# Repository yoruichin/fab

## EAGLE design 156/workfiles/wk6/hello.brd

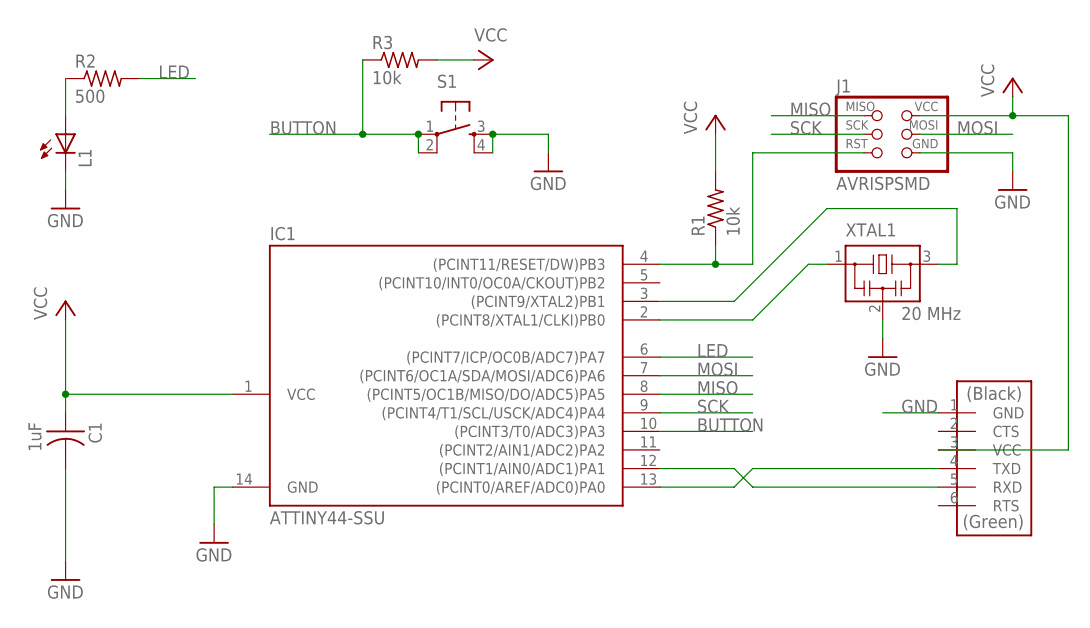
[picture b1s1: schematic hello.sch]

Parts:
C1: 1uF; C1206
IC1: ATTINY44-SSU; SOIC14
J1: AVRISPSMD; 2X03SMD
J2: FTDI; 1X06SMD
L1: LEDFAB1206; LED1206FAB
R1, R3: 10k; R1206
R2: 500; R1206
S1: 6MM_SWITCH6MM_SWITCH; 6MM_SWITCH
XTAL1: 20 MHz; EFOBM

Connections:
BUTTON: IC1.10 ((PCINT3/T0/ADC3)PA3), R3.1, S1.1, S1.2 (P1)
GND: C1.2, IC1.14 (GND), J1.6 (GND), J2.1 (GND), L1.2 (C), S1.3 (S), S1.4 (S1), XTAL1.2
LED: IC1.6 ((PCINT7/ICP/OC0B/ADC7)PA7), R2.2
MISO: IC1.8 ((PCINT5/OC1B/MISO/DO/ADC5)PA5), J1.1 (MISO)
MOSI: IC1.7 ((PCINT6/OC1A/SDA/MOSI/ADC6)PA6), J1.4 (MOSI)
unnamed: L1.1 (A), R2.1
unnamed: IC1.3 ((PCINT9/XTAL2)PB1), XTAL1.3
unnamed: IC1.2 ((PCINT8/XTAL1/CLKI)PB0), XTAL1.1
unnamed: IC1.4 ((PCINT11/RESET/DW)PB3), J1.5 (RST), R1.1
unnamed: IC1.12 ((PCINT1/AIN0/ADC1)PA1), J2.5 (RXD)
unnamed: IC1.13 ((PCINT0/AREF/ADC0)PA0), J2.4 (TXD)
SCK: IC1.9 ((PCINT4/T1/SCL/USCK/ADC4)PA4), J1.3 (SCK)
VCC: C1.1, IC1.1 (VCC), J1.2 (VCC), J2.3 (VCC), R1.2, R3.2

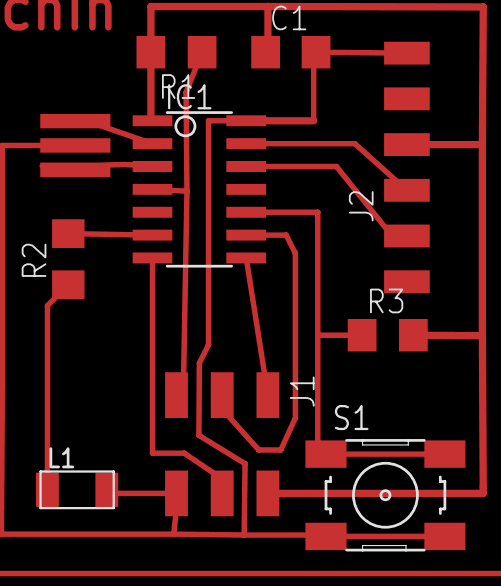
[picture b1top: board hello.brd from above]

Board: 2 copper layers, 10 parts (0 on the bottom side), 13 nets.

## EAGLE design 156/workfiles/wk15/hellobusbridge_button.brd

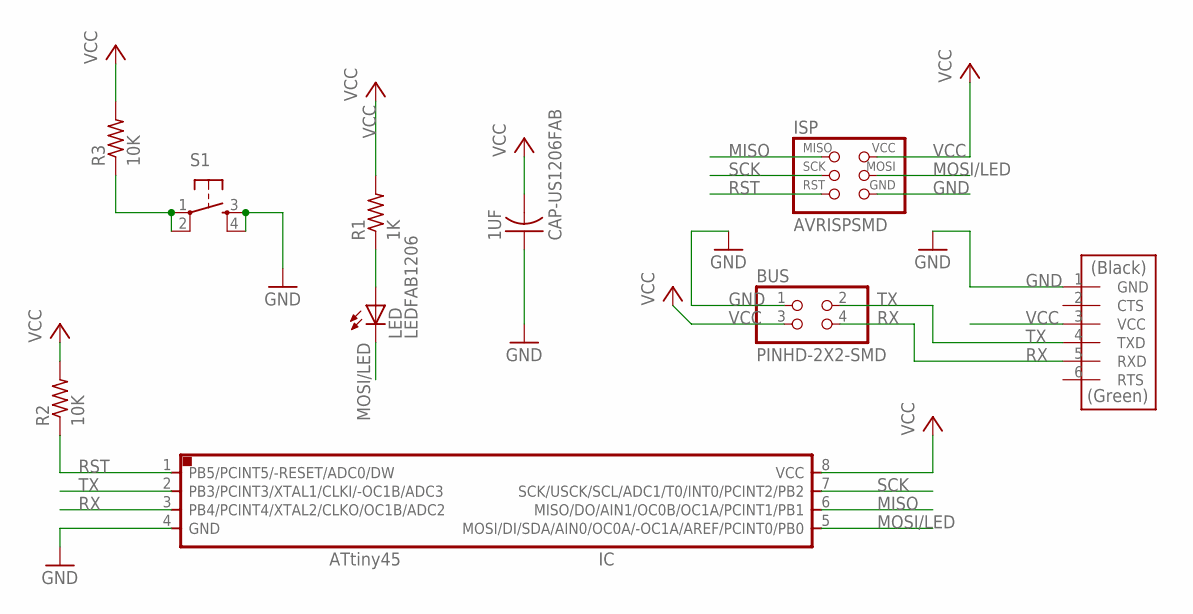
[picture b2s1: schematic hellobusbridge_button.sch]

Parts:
1UF: CAP-US1206FAB; C1206FAB
BUS: PINHD-2X2-SMD; 2X02SMD
IC: IC; SOIC8
ISP: AVRISPSMD; 2X03SMD
LED: LEDFAB1206; LED1206FAB
R1: 1K; R1206FAB
R2, R3: 10K; R1206FAB
S1: 6MM_SWITCH6MM_SWITCH; 6MM_SWITCH
U$5: FTDI-SMD-HEADER; 1X06SMD

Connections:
GND: 1UF.1, BUS.1, IC.4 (GND), ISP.6 (GND), S1.3 (S), S1.4 (S1), U$5.1 (GND)
MISO: IC.6 (MISO/DO/AIN1/OC0B/OC1A/PCINT1/PB1), ISP.1 (MISO), R3.1, S1.1, S1.2 (P1)
MOSI/LED: IC.5 (MOSI/DI/SDA/AIN0/OC0A/-OC1A/AREF/PCINT0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), ISP.4 (MOSI), LED.2 (C)
unnamed: LED.1 (A), R1.1
RST: IC.1 (PB5/PCINT5/-RESET/ADC0/DW), ISP.5 (RST), R2.1
RX: BUS.4, IC.3 (PB4/PCINT4/XTAL2/CLKO/OC1B/ADC2), U$5.5 (RXD)
SCK: IC.7 (SCK/USCK/SCL/ADC1/T0/INT0/PCINT2/PB2), ISP.3 (SCK)
TX: BUS.2, IC.2 (PB3/PCINT3/XTAL1/CLKI/-OC1B/ADC3), U$5.4 (TXD)
VCC: 1UF.2, BUS.3, IC.8 (VCC), ISP.2 (VCC), R1.2, R2.2, R3.2, U$5.3 (VCC)

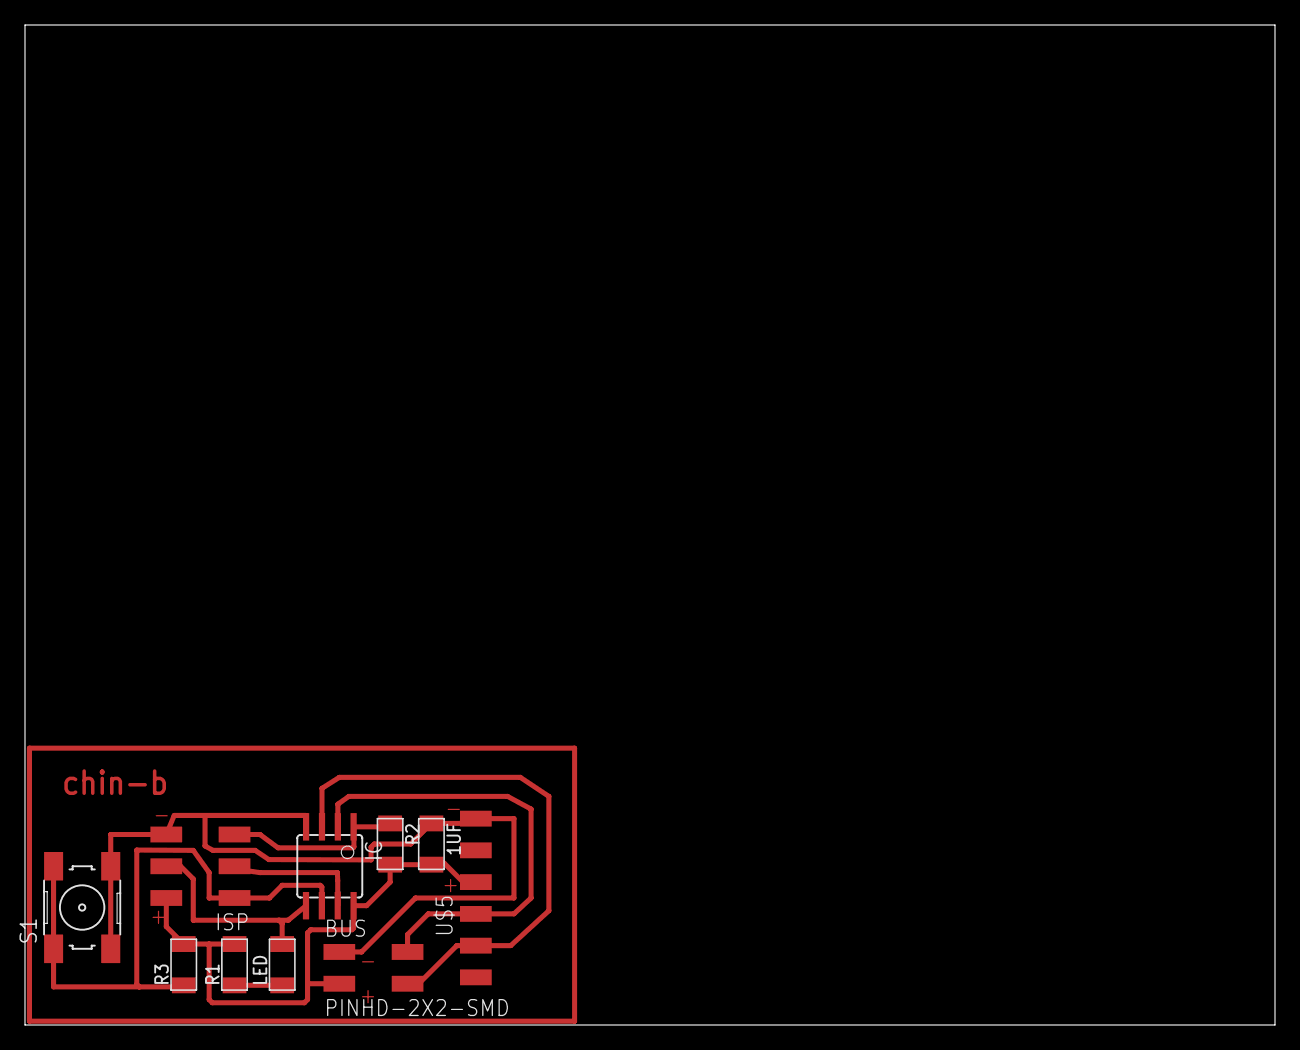
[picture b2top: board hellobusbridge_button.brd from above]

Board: 2 copper layers, 100.0 x 80.0 mm, 10 parts (0 on the bottom side), 9 nets.

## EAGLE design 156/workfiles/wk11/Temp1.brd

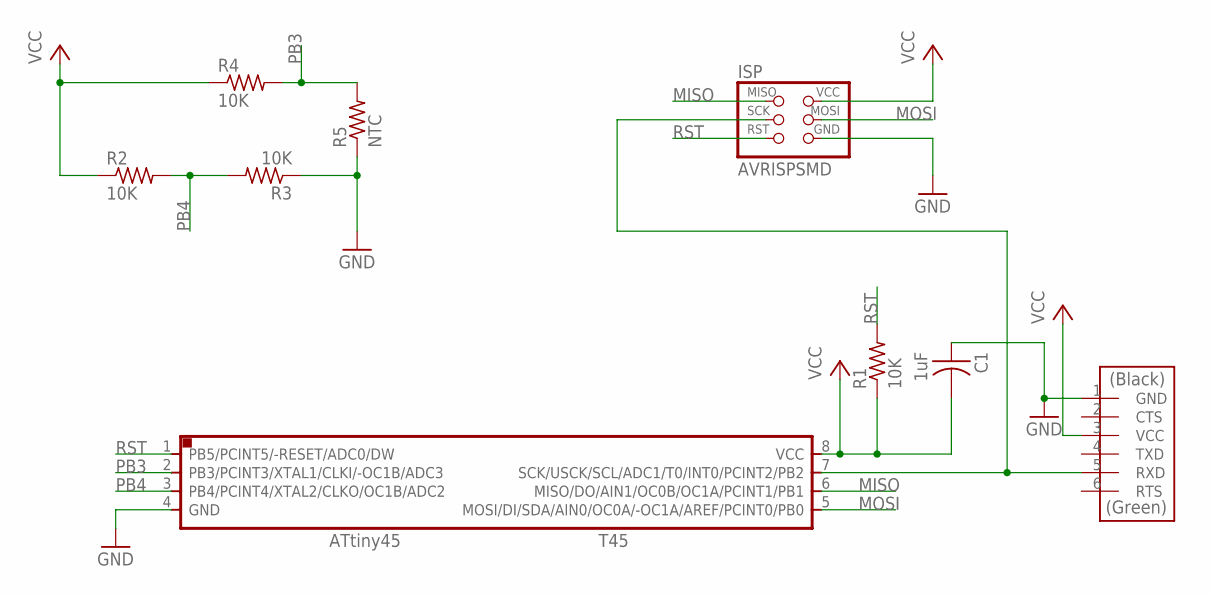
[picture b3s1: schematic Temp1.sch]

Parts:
C1: 1uF; C1206FAB
FDTI: FTDI-SMD-HEADER; 1X06SMD
ISP: AVRISPSMD; 2X03SMD
R1, R2, R3, R4: 10K; R1206FAB
R5: NTC; R1206FAB
T45: ATTINY45SI; SOIC8

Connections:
GND: C1.1, FDTI.1 (GND), ISP.6 (GND), R3.1, R5.1, T45.4 (GND)
MISO: ISP.1 (MISO), T45.6 (MISO/DO/AIN1/OC0B/OC1A/PCINT1/PB1)
MOSI: ISP.4 (MOSI), T45.5 (MOSI/DI/SDA/AIN0/OC0A/-OC1A/AREF/PCINT0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)
unnamed: FDTI.5 (RXD), ISP.3 (SCK), T45.7 (SCK/USCK/SCL/ADC1/T0/INT0/PCINT2/PB2)
PB3: R4.2, R5.2, T45.2 (PB3/PCINT3/XTAL1/CLKI/-OC1B/ADC3)
PB4: R2.2, R3.2, T45.3 (PB4/PCINT4/XTAL2/CLKO/OC1B/ADC2)
RST: ISP.5 (RST), R1.2, T45.1 (PB5/PCINT5/-RESET/ADC0/DW)
VCC: C1.2, FDTI.3 (VCC), ISP.2 (VCC), R1.1, R2.1, R4.1, T45.8 (VCC)

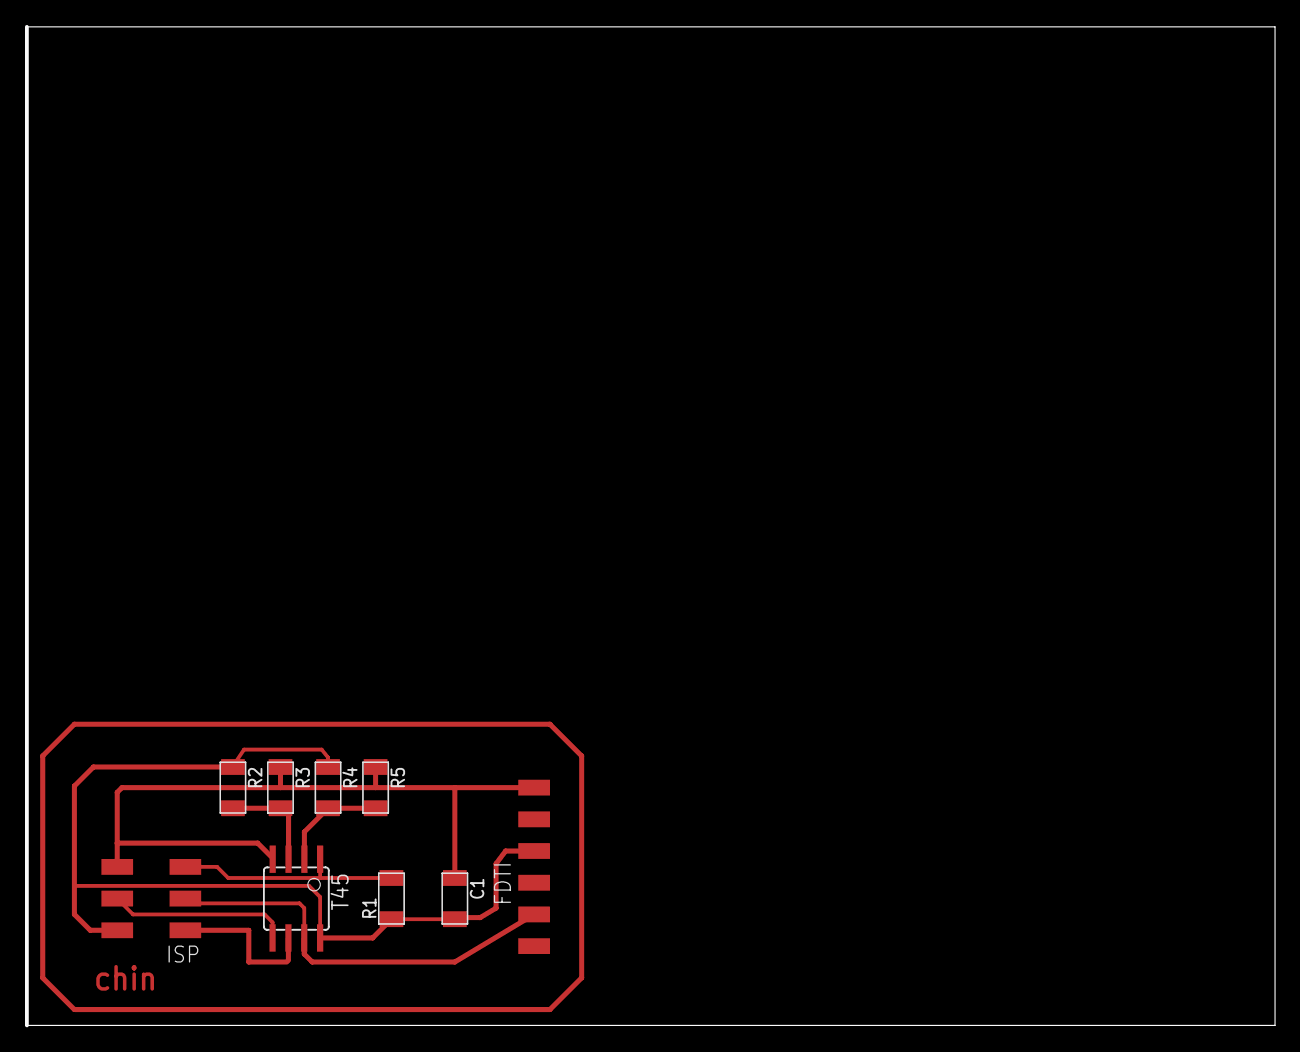
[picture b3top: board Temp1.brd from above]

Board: 2 copper layers, 100.0 x 80.0 mm, 9 parts (0 on the bottom side), 8 nets.

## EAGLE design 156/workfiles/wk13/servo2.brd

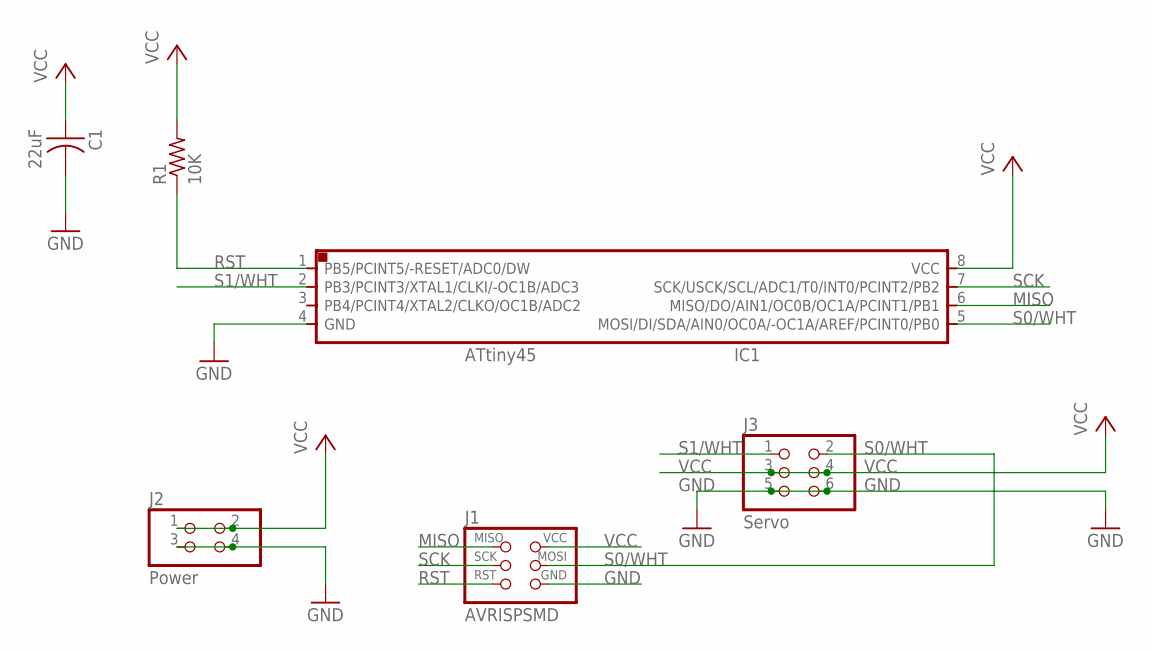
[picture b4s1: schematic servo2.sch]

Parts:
C1: 22uF; C1206FAB
IC1: ATTINY45SI; SOIC8
J1: AVRISPSMD; 2X03SMD
J2: Power; 2X02SMD
J3: Servo; 2X03SMD
R1: 10K; R1206FAB

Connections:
GND: C1.2, IC1.4 (GND), J1.6 (GND), J2.3, J2.4, J3.5, J3.6
MISO: IC1.6 (MISO/DO/AIN1/OC0B/OC1A/PCINT1/PB1), J1.1 (MISO)
RST: IC1.1 (PB5/PCINT5/-RESET/ADC0/DW), J1.5 (RST), R1.1
S0/WHT: IC1.5 (MOSI/DI/SDA/AIN0/OC0A/-OC1A/AREF/PCINT0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), J1.4 (MOSI), J3.2
S1/WHT: IC1.2 (PB3/PCINT3/XTAL1/CLKI/-OC1B/ADC3), J3.1
SCK: IC1.7 (SCK/USCK/SCL/ADC1/T0/INT0/PCINT2/PB2), J1.3 (SCK)
VCC: C1.1, IC1.8 (VCC), J1.2 (VCC), J2.1, J2.2, J3.3, J3.4, R1.2

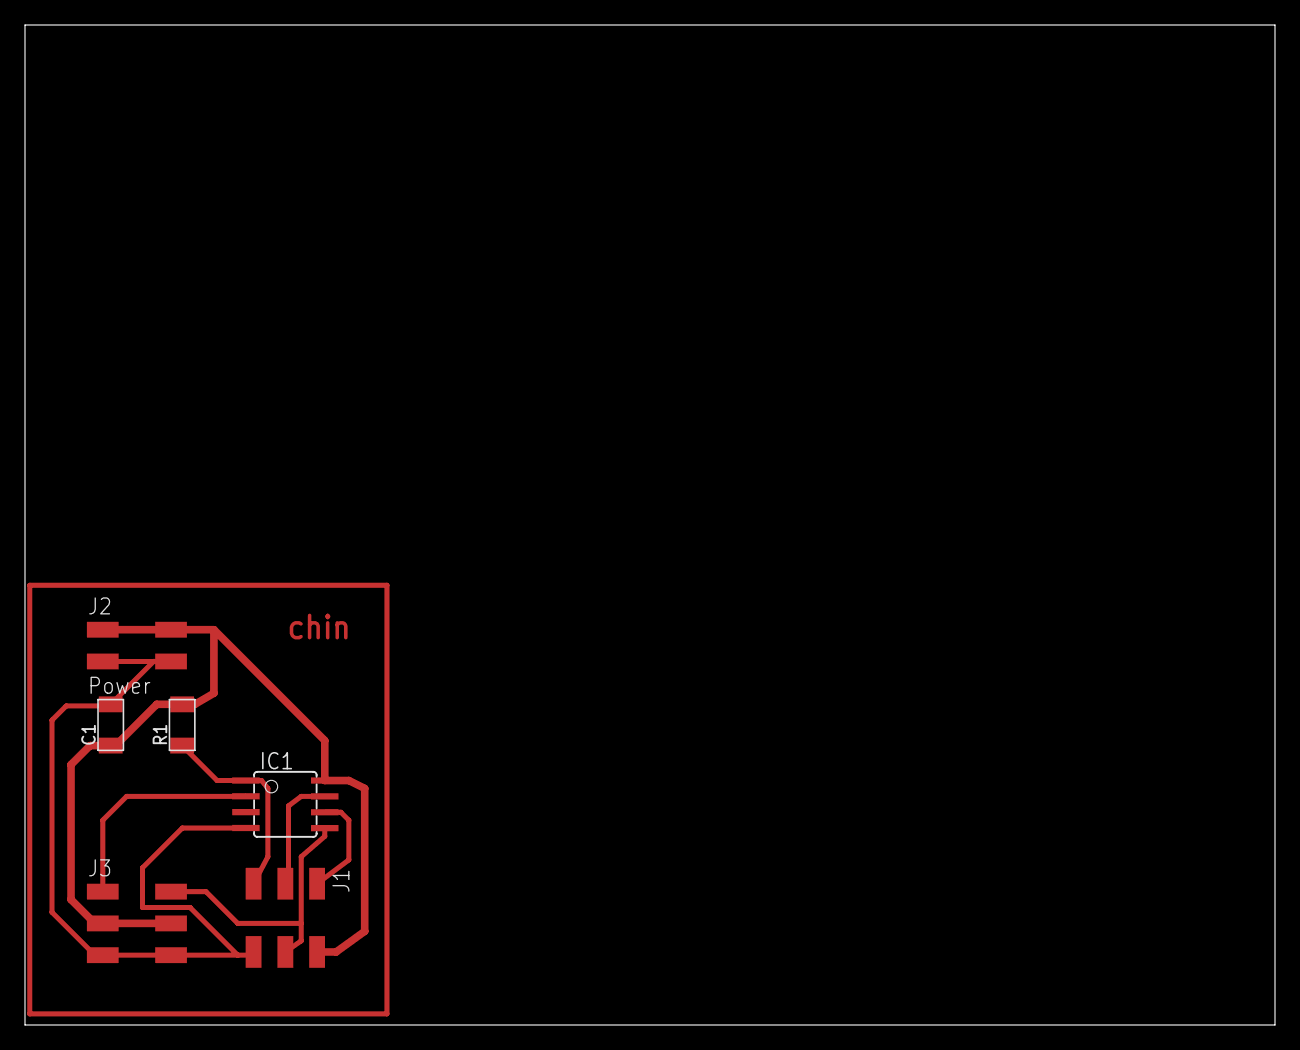
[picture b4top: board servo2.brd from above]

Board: 2 copper layers, 100.0 x 80.0 mm, 6 parts (0 on the bottom side), 7 nets.

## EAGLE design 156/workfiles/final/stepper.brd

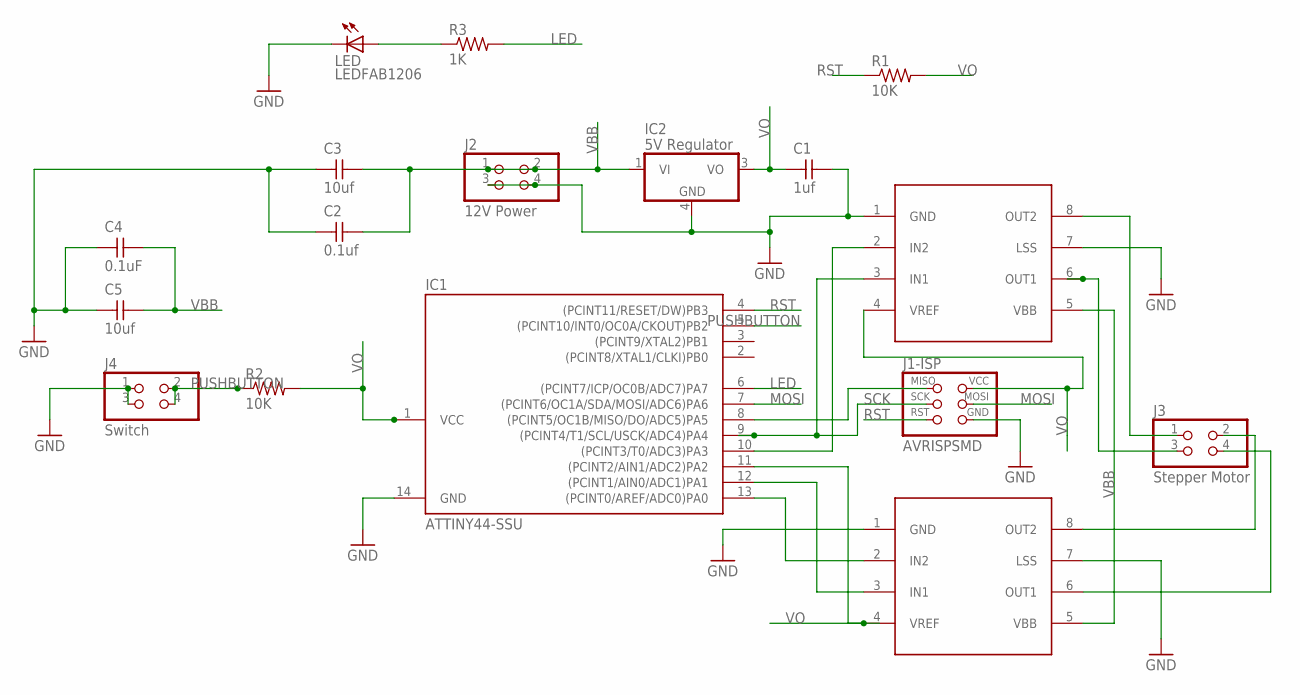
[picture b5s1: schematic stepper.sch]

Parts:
C1: 1uf; C1206FAB
C2: 0.1uf; C1206FAB
C3, C5: 10uf; C1206FAB
C4: 0.1uF; C1206FAB
IC1: ATTINY44-SSU; SOIC14
IC2: 5V Regulator; SOT223
IC3, IC4: A4950; SOIC8
J1-ISP: AVRISPSMD; 2X03SMD
J2: 12V Power; 2X02SMD
J3: Stepper Motor; 2X02SMD
J4: Switch; 2X02SMD
LED: LEDFAB1206; LED1206FAB
R1, R2: 10K; R1206FAB
R3: 1K; R1206FAB

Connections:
GND: C1.2, C2.1, C3.1, C4.1, C5.1, IC1.14 (GND), IC2.4 (GND), IC3.1 (GND), IC3.7 (LSS), IC4.1 (GND), IC4.7 (LSS), J1-ISP.6 (GND), J2.3, J2.4, J4.1, J4.3, LED.2 (C)
LED: IC1.6 ((PCINT7/ICP/OC0B/ADC7)PA7), R3.2
MOSI: IC1.7 ((PCINT6/OC1A/SDA/MOSI/ADC6)PA6), J1-ISP.4 (MOSI)
unnamed: IC1.13 ((PCINT0/AREF/ADC0)PA0), IC3.2 (IN2)
unnamed: IC1.12 ((PCINT1/AIN0/ADC1)PA1), IC3.3 (IN1)
unnamed: IC1.10 ((PCINT3/T0/ADC3)PA3), IC4.2 (IN2)
unnamed: IC4.8 (OUT2), J3.1
unnamed: IC4.6 (OUT1), J3.3
unnamed: IC3.8 (OUT2), J3.2
unnamed: IC1.8 ((PCINT5/OC1B/MISO/DO/ADC5)PA5), J1-ISP.1 (MISO)
unnamed: IC3.6 (OUT1), J3.4
unnamed: LED.1 (A), R3.1
PUSHBUTTON: IC1.5 ((PCINT10/INT0/OC0A/CKOUT)PB2), J4.2, J4.4, R2.1
RST: IC1.4 ((PCINT11/RESET/DW)PB3), J1-ISP.5 (RST), R1.1
SCK: IC1.9 ((PCINT4/T1/SCL/USCK/ADC4)PA4), IC4.3 (IN1), J1-ISP.3 (SCK)
VBB: C2.2, C3.2, C4.2, C5.2, IC2.1 (VI), IC3.5 (VBB), IC4.5 (VBB), J2.1, J2.2
VO: C1.1, IC1.1 (VCC), IC1.11 ((PCINT2/AIN1/ADC2)PA2), IC2.3 (VO), IC3.4 (VREF), IC4.4 (VREF), J1-ISP.2 (VCC), R1.2, R2.2

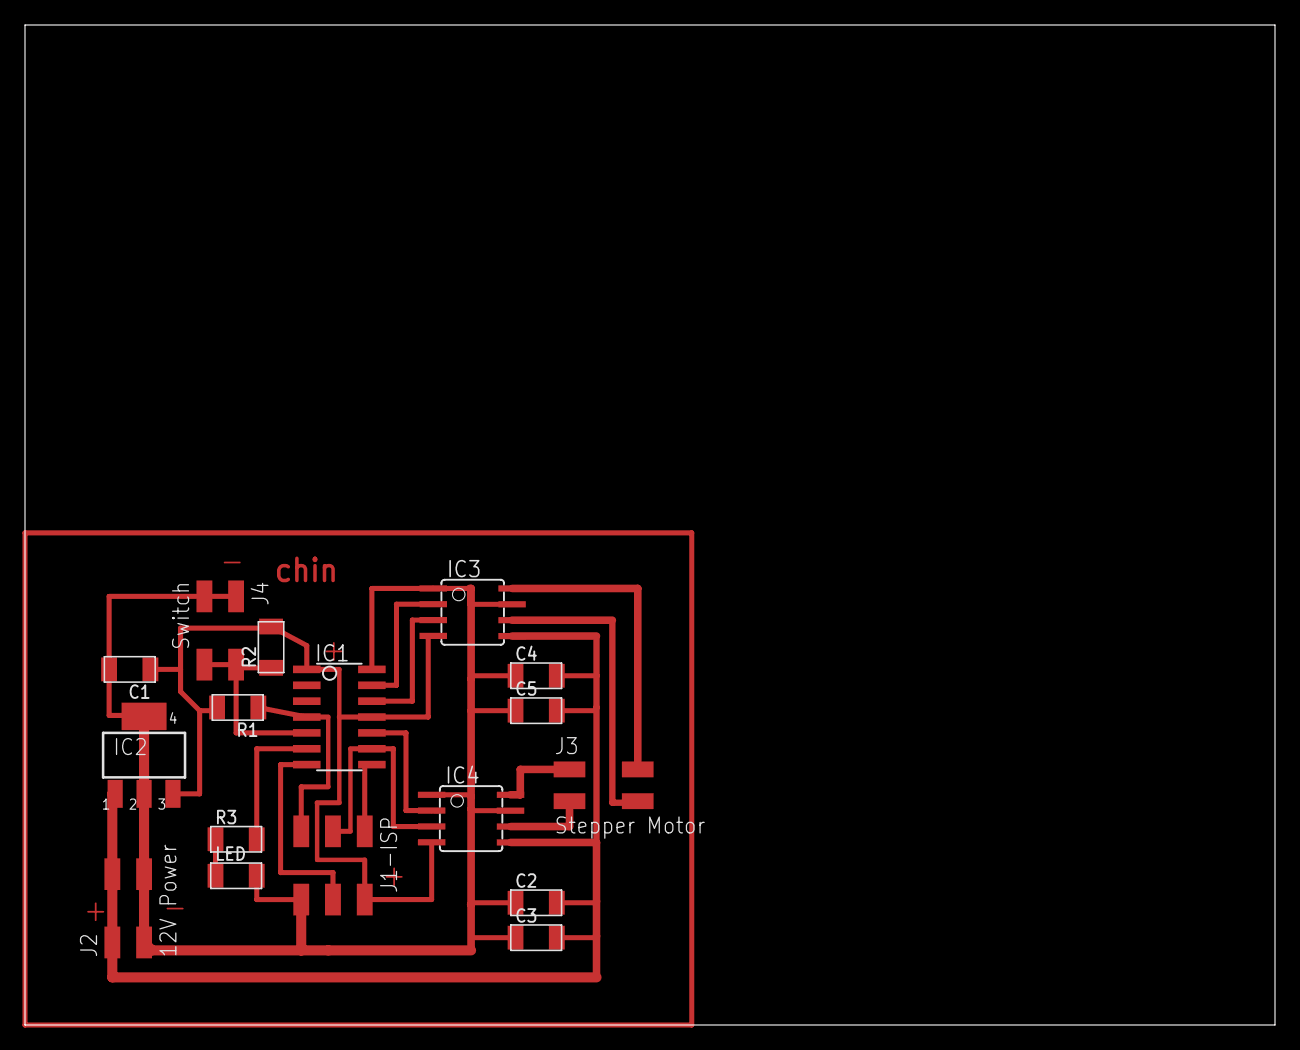
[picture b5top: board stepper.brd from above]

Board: 2 copper layers, 100.0 x 80.0 mm, 17 parts (0 on the bottom side), 17 nets.

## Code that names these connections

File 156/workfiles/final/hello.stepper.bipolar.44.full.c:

//
//
// hello.stepper.bipolar.44.full.c
//
// bipolar full stepping hello-world
//
// Neil Gershenfeld
// 11/21/12
//
// (c) Massachusetts Institute of Technology 2012
// This work may be reproduced, modified, distributed,
// performed, and displayed for any purpose. Copyright is
// retained and must be preserved. The work is provided
// as is; no warranty is provided, and users accept all 
// liability.
//
// Documentation
// =============
// Modified by Yue Siew Chin, Fablab Singapore, 2016
//
// This program causes a stepper motor to turn a page at the press of a pushbutton.
// Microcontroller = ATtiny44
// Pushbutton = PB2
// LED = PA7
// Stepper motor pins = PA0, PA1, PA3, PA4 (A2, A1, B2, B1)
// Bipolar stepper motor 14HS13-0804S
// H-bridge PWM Motor Driver Allegro A4950 
// 5V Regulator LM2940



#include <avr/io.h>
#include <util/delay.h>
#include <avr/interrupt.h>

#define output(directions,pin) (directions |= pin) // set port direction for output
#define input(directions,pin) (directions &= (~pin)) // set port direction for input
#define set(port,pin) (port |= pin) // set port pin
#define clear(port,pin) (port &= (~pin)) // clear port pin
#define toggle(port,pin) (port ^= pin)
#define pin_test(pins,pin) (pins & pin) // test for port pin
#define bit_test(byte,bit) (byte & (1 << bit)) // test for bit set

#define bridge_port PORTA // H-bridge port
#define bridge_direction DDRA // H-bridge direction
#define A2 (1 << PA0) // H-bridge output pins
#define A1 (1 << PA1) // "
#define B2 (1 << PA3) // "
#define B1 (1 << PA4) // "
#define on_delay() _delay_us(35) // PWM on time
#define off_delay() _delay_us(15) // PWM off time
#define PWM_count 100 // number of PWM cycles
#define step_count 53 // number of steps


#define button_port PORTB
#define button_pins PINB
#define button_direction DDRB
#define button (1 << PB2) // set button input pin

#define led_port PORTA
#define led_direction DDRA
#define led (1 << PA7) // set LED output pin


static uint8_t count;

//
// A+ B+ PWM pulse
//
void pulse_ApBp() {
  clear(bridge_port, A2);
  clear(bridge_port, B2);
  set(bridge_port, A1);
  set(bridge_port, B1);
   for (count = 0; count < PWM_count; ++count) {
      set(bridge_port, A1);
      set(bridge_port, B1);
      on_delay();
      clear(bridge_port, A1);
      clear(bridge_port, B1);
      off_delay();
    }
  }
//
// A+ B- PWM pulse
//
void pulse_ApBm() {
  clear(bridge_port, A2);
  clear(bridge_port, B1);
  set(bridge_port, A1);
  set(bridge_port, B2);
   for (count = 0; count < PWM_count; ++count) {
      set(bridge_port, A1);
      set(bridge_port, B2);
      on_delay();
      clear(bridge_port, A1);
      clear(bridge_port, B2);
      off_delay();
    }
  }
//
// A- B+ PWM pulse
//
void pulse_AmBp() {
  clear(bridge_port, A1);
  clear(bridge_port, B2);
  set(bridge_port, A2);
  set(bridge_port, B1);
   for (count = 0; count < PWM_count; ++count) {
      set(bridge_port, A2);
      set(bridge_port, B1);
      on_delay();
      clear(bridge_port, A2);
      clear(bridge_port, B1);
      off_delay();
    }
  }
//
// A- B- PWM pulse
//
void pulse_AmBm() {
  clear(bridge_port, A1);
  clear(bridge_port, B1);
  set(bridge_port, A2);
  set(bridge_port, B2);
   for (count = 0; count < PWM_count; ++count) {
      set(bridge_port, A2);
      set(bridge_port, B2);
      on_delay();
      clear(bridge_port, A2);
      clear(bridge_port, B2);
      off_delay();
    }
  }
//
// clockwise step
//
void step_cw() {
   pulse_ApBp();
   pulse_AmBp();
   pulse_AmBm();
   pulse_ApBm();
}
//
// counter-clockwise step
//
void step_ccw() {
   pulse_ApBm();
   pulse_AmBm();
   pulse_AmBp();
   pulse_ApBp();
}

uint8_t debounce(void) {                      // check for button bounce
  if (bit_is_clear(button_pins, button)) {     // button is pressed
    _delay_us(1000);                          // debounce timeout in microseconds
    if (bit_is_clear(button_pins, button)) {   // button is still pressed after a short delay
      return (1);       // return true
    }
  }
  return (0);           // otherwise return false
} 

int main(void) {
   //
   // main
   //
   static uint8_t i,j;
   //
   // set clock divider to /1
   //
   CLKPR = (1 << CLKPCE);
   CLKPR = (0 << CLKPS3) | (0 << CLKPS2) | (0 << CLKPS1) | (0 << CLKPS0);
   //
   // initialize bridge pins
   //
   clear(bridge_port, A1);
   output(bridge_direction, A1);
   clear(bridge_port, A2);
   output(bridge_direction, A2);
   clear(bridge_port, B1);
   output(bridge_direction, B1);
   clear(bridge_port, B2);
   output(bridge_direction, B2);

   input(button_direction, button);  // clear bit
   // set(button_port, button);         // value = HIGH; enable pull-up on the button
   output(led_direction, led);   // set bit of LED for output
   set(led_port, led);

   //
   // main loop
   //
  while (1) {

    if (bit_is_clear(PINB, PB2)) {
      clear(led_port, led); 
      for (i = 0; i < step_count; ++i) {
//          for (j = 0; j < i; ++j)
          step_cw();
        _delay_ms(10); 

//  stop stepper motor rotation
           clear(bridge_port, A1);
           clear(bridge_port, A2);
           clear(bridge_port, B1);
           clear(bridge_port, B2);

      }         
    }
    else {
      set(led_port, led);   // indicates ready to receive input
   }
  }
}

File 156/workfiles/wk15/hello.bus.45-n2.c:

//
//
// hello.bus.45.c
//
// 9600 baud serial bus hello-world
//
// Neil Gershenfeld
// 11/24/10
//
// (c) Massachusetts Institute of Technology 2010
// Permission granted for experimental and personal use;
// license for commercial sale available from MIT.
//

#include <avr/io.h>
#include <util/delay.h>
#include <avr/pgmspace.h>
#include <string.h>

#define output(directions,pin) (directions |= pin) // set port direction for output
#define input(directions,pin) (directions &= (~pin)) // set port direction for input
#define set(port,pin) (port |= pin) // set port pin
#define clear(port,pin) (port &= (~pin)) // clear port pin
#define pin_test(pins,pin) (pins & pin) // test for port pin
#define bit_test(byte,bit) (byte & (1 << bit)) // test for bit set
#define bit_delay_time 100 // bit delay for 9600 with overhead
#define bit_delay() _delay_us(bit_delay_time) // RS232 bit delay
#define half_bit_delay() _delay_us(bit_delay_time/2) // RS232 half bit delay
#define led_delay() _delay_ms(100) // LED flash delay

#define led_port PORTB
#define led_direction DDRB
#define led_pin (1 << PB0)

//#define button_port PORTB
//#define button_direction DDRB
//#define button_pin (1 << PB1)

#define serial_port PORTB
#define serial_direction DDRB
#define serial_pins PINB
#define serial_pin_in (1 << PB3)
#define serial_pin_out (1 << PB4)

#define node_id '2'  // to hard code for each host / slave node

void get_char(volatile unsigned char *pins, unsigned char pin, char *rxbyte) {
   //
   // read character into rxbyte on pins pin
   //    assumes line driver (inverts bits)
   //
   *rxbyte = 0;
   while (pin_test(*pins,pin))
      //
      // wait for start bit
      //
      ;
   //
   // delay to middle of first data bit
   //
   half_bit_delay();
   bit_delay();
   //
   // unrolled loop to read data bits
   //
   if pin_test(*pins,pin)
      *rxbyte |= (1 << 0);
   else
      *rxbyte |= (0 << 0);
   bit_delay();
   if pin_test(*pins,pin)
      *rxbyte |= (1 << 1);
   else
      *rxbyte |= (0 << 1);
   bit_delay();
   if pin_test(*pins,pin)
      *rxbyte |= (1 << 2);
   else
      *rxbyte |= (0 << 2);
   bit_delay();
   if pin_test(*pins,pin)
      *rxbyte |= (1 << 3);
   else
      *rxbyte |= (0 << 3);
   bit_delay();
   if pin_test(*pins,pin)
      *rxbyte |= (1 << 4);
   else
      *rxbyte |= (0 << 4);
   bit_delay();
   if pin_test(*pins,pin)
      *rxbyte |= (1 << 5);
   else
      *rxbyte |= (0 << 5);
   bit_delay();
   if pin_test(*pins,pin)
      *rxbyte |= (1 << 6);
   else
      *rxbyte |= (0 << 6);
   bit_delay();
   if pin_test(*pins,pin)
      *rxbyte |= (1 << 7);
   else
      *rxbyte |= (0 << 7);
   //
   // wait for stop bit
   //
   bit_delay();
   half_bit_delay();
   }

void put_char(volatile unsigned char *port, unsigned char pin, char txchar) {
   //
   // send character in txchar on port pin
   //    assumes line driver (inverts bits)
   //
   // start bit
   //
   clear(*port,pin);
   bit_delay();
   //
   // unrolled loop to write data bits
   //
   if bit_test(txchar,0)
      set(*port,pin);
   else
      clear(*port,pin);
   bit_delay();
   if bit_test(txchar,1)
      set(*port,pin);
   else
      clear(*port,pin);
   bit_delay();
   if bit_test(txchar,2)
      set(*port,pin);
   else
      clear(*port,pin);
   bit_delay();
   if bit_test(txchar,3)
      set(*port,pin);
   else
      clear(*port,pin);
   bit_delay();
   if bit_test(txchar,4)
      set(*port,pin);
   else
      clear(*port,pin);
   bit_delay();
   if bit_test(txchar,5)
      set(*port,pin);
   else
      clear(*port,pin);
   bit_delay();
   if bit_test(txchar,6)
      set(*port,pin);
   else
      clear(*port,pin);
   bit_delay();
   if bit_test(txchar,7)
      set(*port,pin);
   else
      clear(*port,pin);
   bit_delay();
   //
   // stop bit
   //
   set(*port,pin);
   bit_delay();
   //
   // char delay
   //
   bit_delay();
   }

void put_string(volatile unsigned char *port, unsigned char pin, PGM_P str) {
   //
   // send character in txchar on port pin
   //    assumes line driver (inverts bits)
   //
   static char chr;
   static int index;
   index = 0;
   do {
      chr = pgm_read_byte(&(str[index]));
      put_char(&serial_port, serial_pin_out, chr);
      ++index;
      } while (chr != 0);
   }

void flash() {
   //
   // LED flash delay
   //
   clear(led_port, led_pin);
   led_delay();
   set(led_port, led_pin);
   }

int main(void) {
   //
   // main
   //
   static char chr;
   //
   // set clock divider to /1
   //
   CLKPR = (1 << CLKPCE);
   CLKPR = (0 << CLKPS3) | (0 << CLKPS2) | (0 << CLKPS1) | (0 << CLKPS0);
   //
   // initialize output pins
   //
   set(serial_port, serial_pin_out);
   input(serial_direction, serial_pin_out);
   set(led_port, led_pin);
   output(led_direction, led_pin);
   //
   // main loop
   //
   while (1) {
      get_char(&serial_pins, serial_pin_in, &chr);
      flash();
      if (chr == node_id) {
         output(serial_direction, serial_pin_out);
         static const char message[] PROGMEM = "node ";
         put_string(&serial_port, serial_pin_out, (PGM_P) message);
         put_char(&serial_port, serial_pin_out, chr);
         put_char(&serial_port, serial_pin_out, 10); // new line
         led_delay();
         flash();
         led_delay();
         flash();
         input(serial_direction, serial_pin_out);
         }
      }
   }

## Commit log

2016-07-05 uploaded fab
2016-07-05 added gitignore and gitattributes
2016-07-05 updated pages
2016-10-14 added projects folder
2016-10-20 added fab12
